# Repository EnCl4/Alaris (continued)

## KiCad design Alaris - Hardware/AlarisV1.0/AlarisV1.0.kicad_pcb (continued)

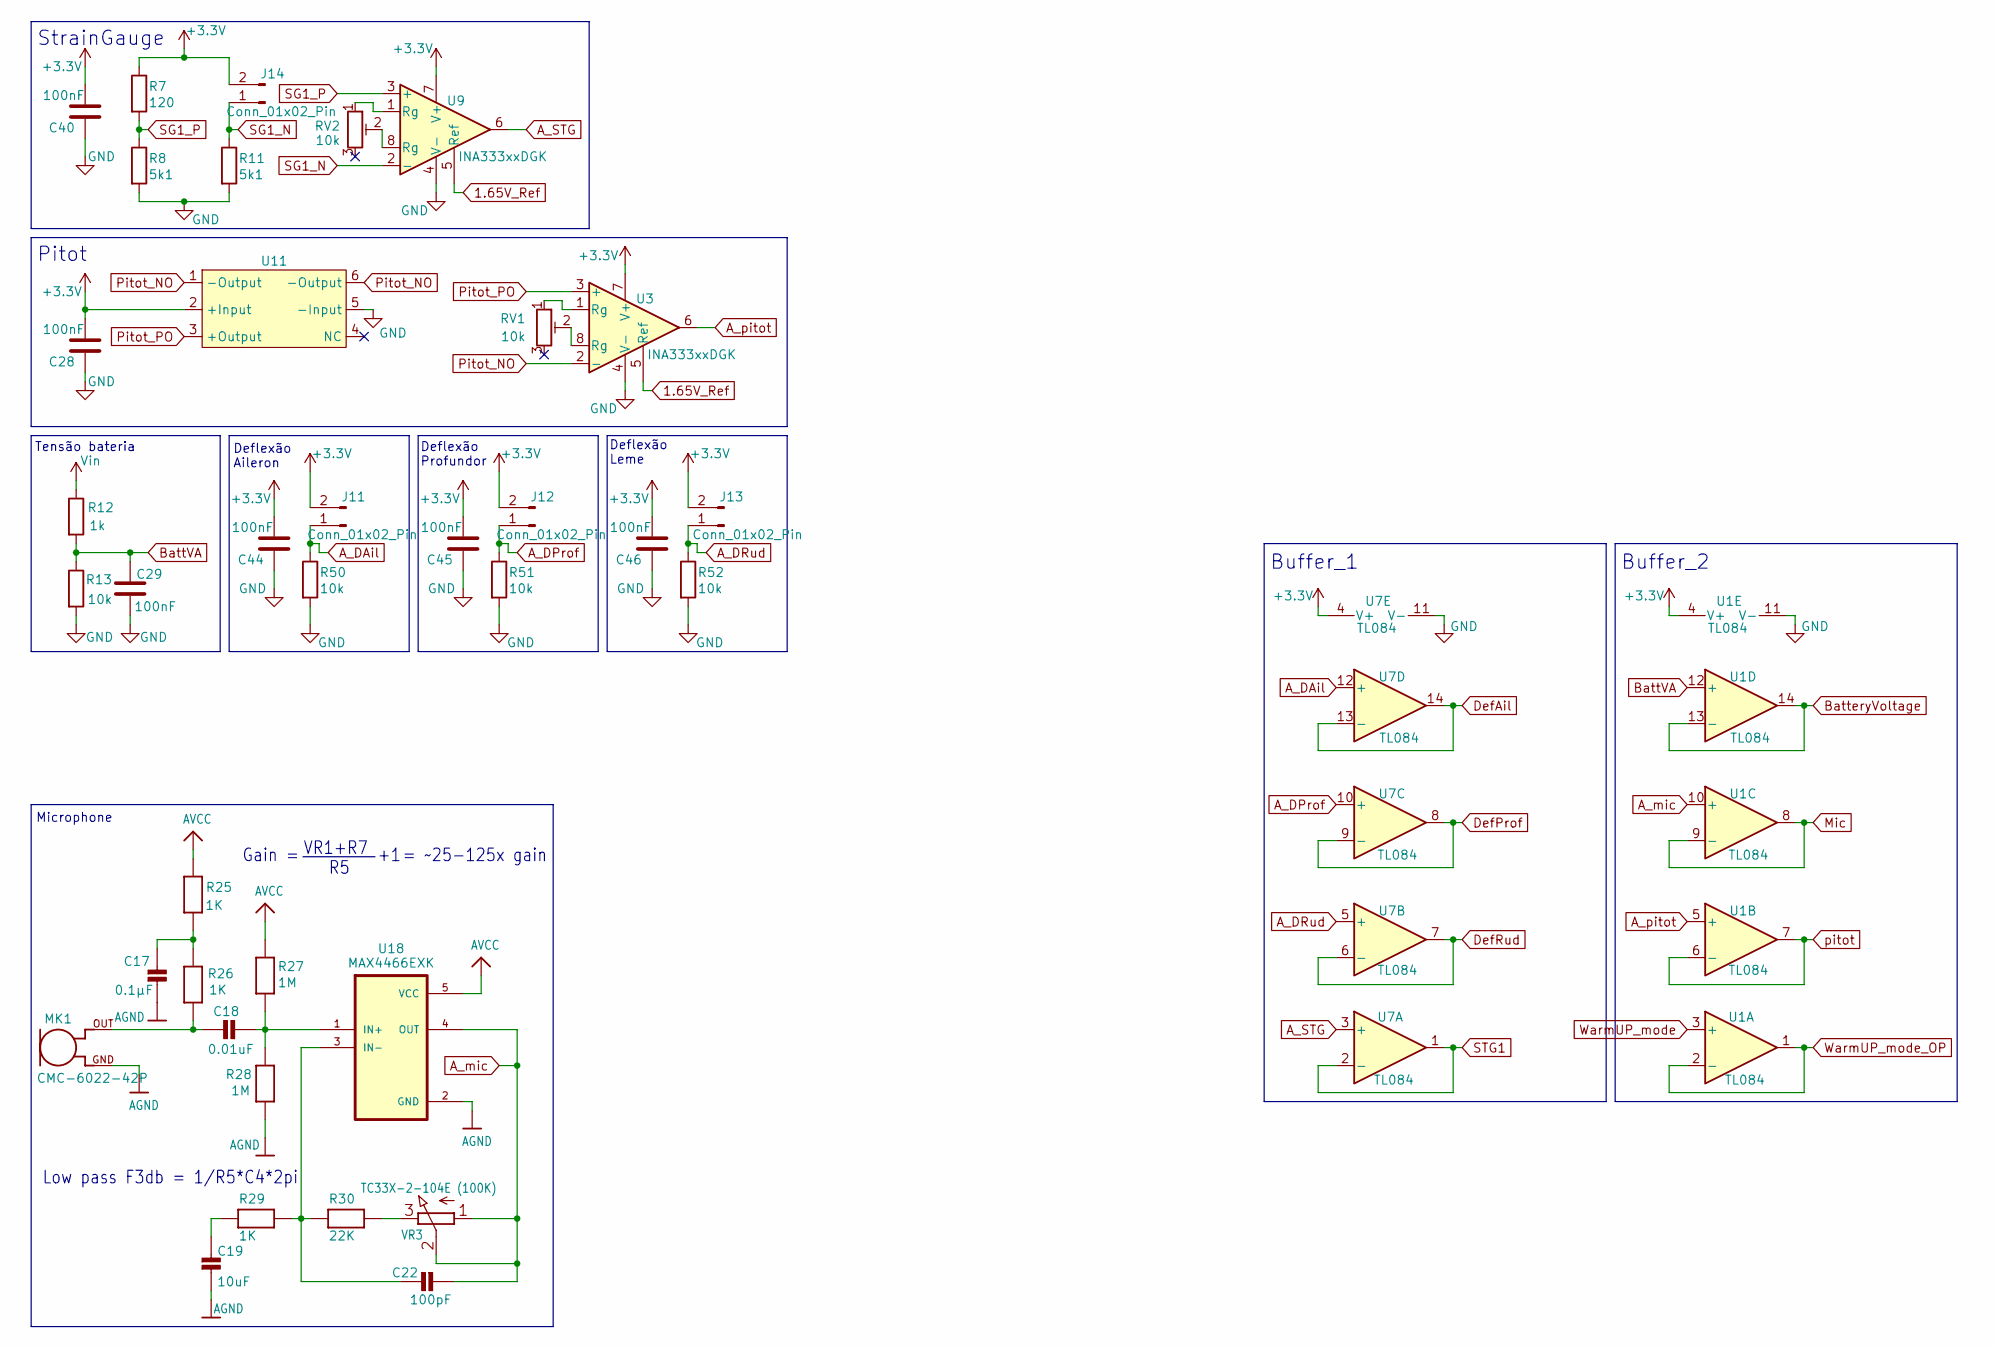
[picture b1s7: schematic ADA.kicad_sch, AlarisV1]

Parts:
C17: 0.1µF; C_0603_1608Metric_Pad1.08x0.95mm_HandSolder
C18: 0.01uF; C_0603_1608Metric_Pad1.08x0.95mm_HandSolder
C19: 10uF; C_0603_1608Metric_Pad1.08x0.95mm_HandSolder
C22: 100pF; C_0603_1608Metric_Pad1.08x0.95mm_HandSolder
C28, C29, C40, C44, C45, C46: 100nF; C_0603_1608Metric_Pad1.08x0.95mm_HandSolder
J11, J12, J13, J14: Conn_01x02_Pin; JST_EH_B2B-EH-A_1x02_P2.50mm_Vertical
MK1: CMC-6022-42P; Mic6022; PARTREV 1
R7: 120; R_0603_1608Metric_Pad0.98x0.95mm_HandSolder
R8, R11: 5k1; R_0603_1608Metric_Pad0.98x0.95mm_HandSolder
R12: 1k; R_0603_1608Metric_Pad0.98x0.95mm_HandSolder
R13, R50, R51, R52: 10k; R_0603_1608Metric_Pad0.98x0.95mm_HandSolder
R25, R26, R29: 1K; R_0603_1608Metric_Pad0.98x0.95mm_HandSolder
R27, R28: 1M; R_0603_1608Metric_Pad0.98x0.95mm_HandSolder
R30: 22K; R_0603_1608Metric_Pad0.98x0.95mm_HandSolder
RV1, RV2: 10k; Potentiometer_Bourns_TC33X_Vertical
U1, U7: TL084; SOIC-14_3.9x8.7mm_P1.27mm
U3, U9: INA333xxDGK; VSSOP-8_3x3mm_P0.65mm
U11: MPS20N0040D
U18: MAX4466EXK; MAX4466
VR3: TC33X-2-104E (100K); Potentiometer_Bourns_TC33X_Vertical

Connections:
1.65V_Ref: U3.5 (Ref), U9.5 (Ref); also elsewhere on the board
+3.3V: C28.2, C40.2, C44.2, C45.2, C46.2, J11.2, J12.2, J13.2, J14.2, R7.1, U1.4 (V+), U3.7 (V+), U7.4 (V+), U9.7 (V+), U11.2 (+Input); also elsewhere on the board
AGND: C17.2, C19.2, MK1.GND, R28.1, U18.2 (GND); also elsewhere on the board
AVCC: R25.2, R27.2, U18.5 (VCC); also elsewhere on the board
A_DAil: J11.1, R50.1, U7.12 (+)
A_DProf: J12.1, R51.1, U7.10 (+)
A_DRud: J13.1, R52.1, U7.5 (+)
A_STG: U7.3 (+), U9.6
A_mic: C22.1, U1.10 (+), U18.4 (OUT), VR3.1 (A), VR3.2 (S)
A_pitot: U1.5 (+), U3.6
BattVA: C29.1, R12.2, R13.1, U1.12 (+)
BatteryVoltage: U1.13 (-), U1.14; also elsewhere on the board
DefAil: U7.13 (-), U7.14; also elsewhere on the board
DefProf: U7.8, U7.9 (-); also elsewhere on the board
DefRud: U7.6 (-), U7.7; also elsewhere on the board
GND: C28.1, C29.2, C40.1, C44.1, C45.1, C46.1, R8.2, R11.2, R13.2, R50.2, R51.2, R52.2, U1.11 (V-), U3.4 (V-), U7.11 (V-), U9.4 (V-), U11.5 (-Input); also elsewhere on the board
Mic: U1.8, U1.9 (-); also elsewhere on the board
unnamed: C17.1, R25.1, R26.2
unnamed: C18.1, MK1.OUT, R26.1
unnamed: C18.2, R27.1, R28.2, U18.1 (IN+)
unnamed: C19.1, R29.1
unnamed: C22.2, R29.2, R30.1, U18.3 (IN-)
unnamed: RV1.1, U3.1 (Rg)
unnamed: RV1.2, U3.8 (Rg)
unnamed: RV2.1, U9.1 (Rg)
unnamed: RV2.2, U9.8 (Rg)
unnamed: R30.2, VR3.3 (E)
Pitot_NO: U3.2 (-), U11.1 (-Output), U11.6 (-Output)
Pitot_PO: U3.3 (+), U11.3 (+Output)
SG1_N: J14.1, R11.1, U9.2 (-)
SG1_P: R7.2, R8.1, U9.3 (+)
STG1: U7.1, U7.2 (-); also elsewhere on the board
Vin: R12.1; also elsewhere on the board
WarmUP_mode: U1.3 (+); also elsewhere on the board
WarmUP_mode_OP: U1.1, U1.2 (-); also elsewhere on the board
pitot: U1.6 (-), U1.7; also elsewhere on the board

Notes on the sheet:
Tensão bateria
StrainGauge
Deflexão Aileron
Microphone
Buffer_1
Deflexão Leme
Gain =
Buffer_2
Low pass F3db = 1/R5*C4*2pi
Deflexão Profundor
VR1+R7
Pitot
= ~25-125x gain

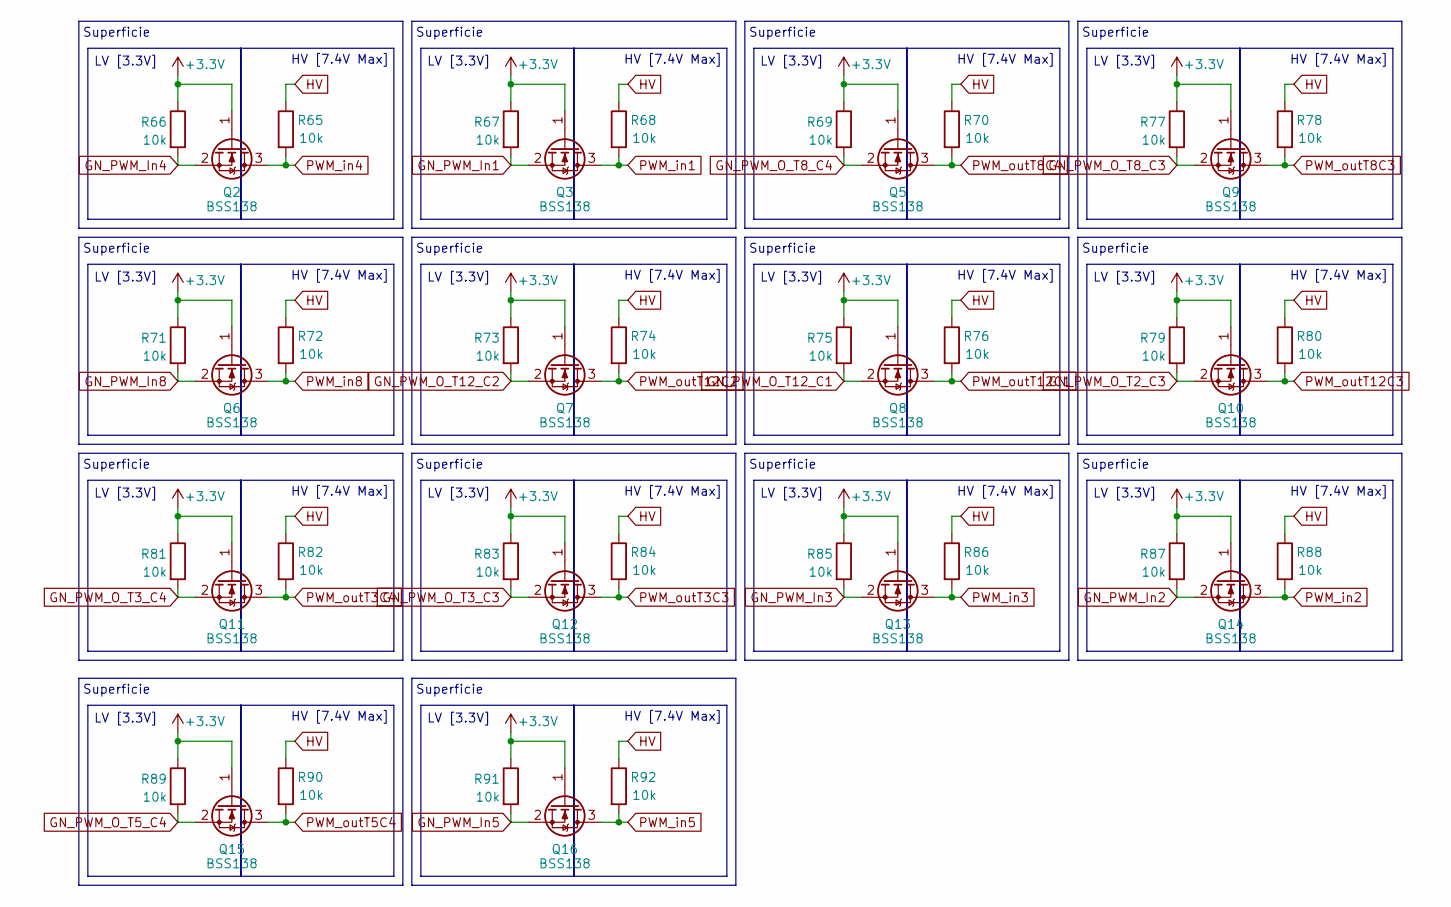
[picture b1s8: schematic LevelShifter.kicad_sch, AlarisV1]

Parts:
Q2, Q3, Q5, Q6, Q7, Q8, Q9, Q10, Q11, Q12, Q13, Q14, Q15, Q16: BSS138; SOT-23
R65, R66, R67, R68, R69, R70, R71, R72, R73, R74, R75, R76, R77, R78, R79, R80, R81, R82, R83, R84, R85, R86, R87, R88, R89, R90, R91, R92: 10k; R_0603_1608Metric_Pad0.98x0.95mm_HandSolder

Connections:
+3.3V: Q2.1 (G), Q3.1 (G), Q5.1 (G), Q6.1 (G), Q7.1 (G), Q8.1 (G), Q9.1 (G), Q10.1 (G), Q11.1 (G), Q12.1 (G), Q13.1 (G), Q14.1 (G), Q15.1 (G), Q16.1 (G), R66.1, R67.1, R69.1, R71.1, R73.1, R75.1, R77.1, R79.1, R81.1, R83.1, R85.1, R87.1, R89.1, R91.1; also elsewhere on the board
GN_PWM_In1: Q3.2 (S), R67.2; also elsewhere on the board
GN_PWM_In2: Q14.2 (S), R87.2; also elsewhere on the board
GN_PWM_In3: Q13.2 (S), R85.2; also elsewhere on the board
GN_PWM_In4: Q2.2 (S), R66.2; also elsewhere on the board
GN_PWM_In5: Q16.2 (S), R91.2; also elsewhere on the board
GN_PWM_In8: Q6.2 (S), R71.2; also elsewhere on the board
GN_PWM_O_T2_C3: Q10.2 (S), R79.2; also elsewhere on the board
GN_PWM_O_T3_C3: Q12.2 (S), R83.2; also elsewhere on the board
GN_PWM_O_T3_C4: Q11.2 (S), R81.2; also elsewhere on the board
GN_PWM_O_T5_C4: Q15.2 (S), R89.2; also elsewhere on the board
GN_PWM_O_T8_C3: Q9.2 (S), R77.2; also elsewhere on the board
GN_PWM_O_T8_C4: Q5.2 (S), R69.2; also elsewhere on the board
GN_PWM_O_T12_C1: Q8.2 (S), R75.2; also elsewhere on the board
GN_PWM_O_T12_C2: Q7.2 (S), R73.2; also elsewhere on the board
HV: R65.1, R68.1, R70.1, R72.1, R74.1, R76.1, R78.1, R80.1, R82.1, R84.1, R86.1, R88.1, R90.1, R92.1; also elsewhere on the board
PWM_in1: Q3.3 (D), R68.2; also elsewhere on the board
PWM_in2: Q14.3 (D), R88.2; also elsewhere on the board
PWM_in3: Q13.3 (D), R86.2; also elsewhere on the board
PWM_in4: Q2.3 (D), R65.2; also elsewhere on the board
PWM_in5: Q16.3 (D), R92.2; also elsewhere on the board
PWM_in8: Q6.3 (D), R72.2; also elsewhere on the board
PWM_outT3C3: Q12.3 (D), R84.2; also elsewhere on the board
PWM_outT3C4: Q11.3 (D), R82.2; also elsewhere on the board
PWM_outT5C4: Q15.3 (D), R90.2; also elsewhere on the board
PWM_outT8C3: Q9.3 (D), R78.2; also elsewhere on the board
PWM_outT8C4: Q5.3 (D), R70.2; also elsewhere on the board
PWM_outT12C1: Q8.3 (D), R76.2; also elsewhere on the board
PWM_outT12C2: Q7.3 (D), R74.2; also elsewhere on the board
PWM_outT12C3: Q10.3 (D), R80.2; also elsewhere on the board

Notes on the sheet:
HV [7.4V Max]
LV [3.3V]
Superficie

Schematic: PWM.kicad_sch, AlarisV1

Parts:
J8, J9, J10, J15, J16, J17, J18, J19, J20, J21, J22, J23, J24, J25: Conn_01x03_Pin; JST_EH_B3B-EH-A_1x03_P2.50mm_Vertical

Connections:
GND: J8.3, J9.3, J10.3, J15.3, J16.3, J17.3, J18.3, J19.3, J20.3, J21.3, J22.3, J23.3, J24.3, J25.3; also elsewhere on the board
HV: J8.2, J9.2, J10.2, J15.2, J16.2, J17.2, J18.2, J19.2, J20.2, J21.2, J22.2, J23.2, J24.2, J25.2; also elsewhere on the board
PWM_in1: J9.1; also elsewhere on the board
PWM_in2: J23.1; also elsewhere on the board
PWM_in3: J22.1; also elsewhere on the board
PWM_in4: J8.1; also elsewhere on the board
PWM_in5: J25.1; also elsewhere on the board
PWM_in8: J15.1; also elsewhere on the board
PWM_outT3C3: J20.1; also elsewhere on the board
PWM_outT3C4: J21.1; also elsewhere on the board
PWM_outT5C4: J24.1; also elsewhere on the board
PWM_outT8C3: J16.1; also elsewhere on the board
PWM_outT8C4: J10.1; also elsewhere on the board
PWM_outT12C1: J18.1; also elsewhere on the board
PWM_outT12C2: J19.1; also elsewhere on the board
PWM_outT12C3: J17.1; also elsewhere on the board

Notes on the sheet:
Signal

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
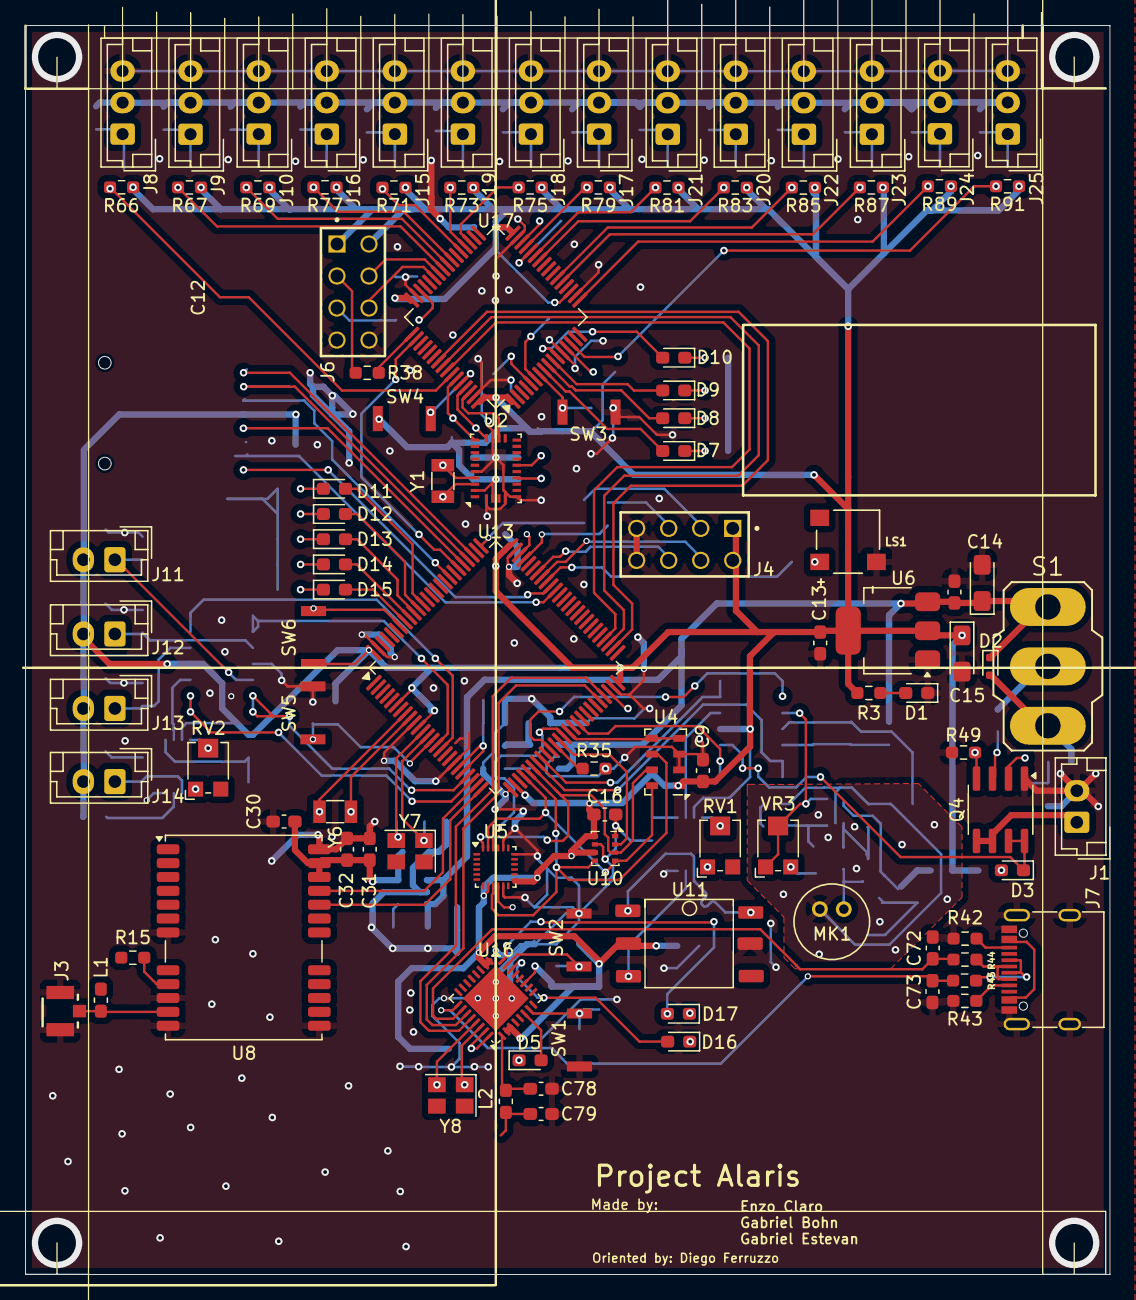
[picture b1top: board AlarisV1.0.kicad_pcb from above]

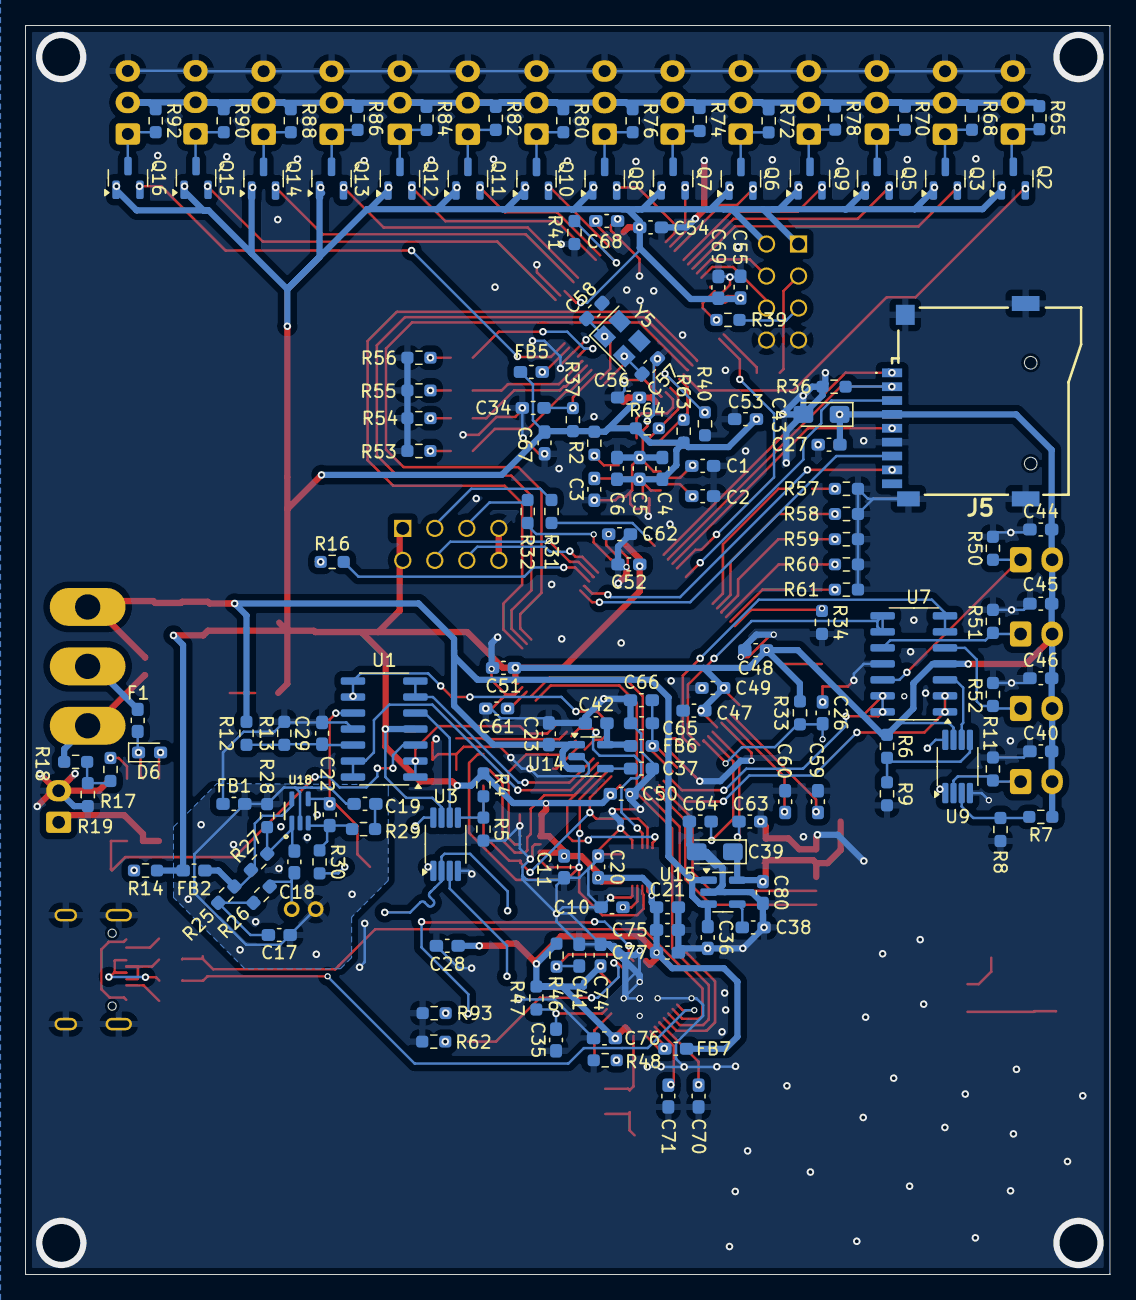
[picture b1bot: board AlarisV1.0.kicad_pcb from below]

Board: 2 copper layers, 86.0 x 99.1 mm, 258 parts (155 on the bottom side), 177 nets.

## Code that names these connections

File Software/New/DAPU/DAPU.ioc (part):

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board=custom
Mcu.Name=STM32H723VGTx
Mcu.Package=LQFP100
Mcu.UserName=STM32H723VGTx
PA0.Mode=IN16-Single-Ended
PA0.Signal=ADC1_INP16
PA1.Mode=IN17-Single-Ended
PA1.Signal=ADC1_INP17
PA10.Mode=Asynchronous
PA10.Signal=USART1_RX
PA13(JTMS/SWDIO).Mode=Serial_Wire
PA13(JTMS/SWDIO).Signal=DEBUG_JTMS-SWDIO
PA14(JTCK/SWCLK).Mode=Serial_Wire
PA14(JTCK/SWCLK).Signal=DEBUG_JTCK-SWCLK
PA2.Mode=Asynchronous
PA2.Signal=USART2_TX
PA3.Signal=GPIO_Analog
PA5.GPIO_Speed=GPIO_SPEED_FREQ_VERY_HIGH
PA5.GPIOParameters=GPIO_Speed
PA5.Mode=Full_Duplex_Master
PA5.Signal=SPI1_SCK
PA6.GPIO_Speed=GPIO_SPEED_FREQ_VERY_HIGH
PA6.GPIOParameters=GPIO_Speed
PA6.Mode=Full_Duplex_Master
PA6.Signal=SPI1_MISO
PA7.GPIO_Speed=GPIO_SPEED_FREQ_VERY_HIGH
PA7.GPIOParameters=GPIO_Speed
PA7.Mode=Full_Duplex_Master
PA7.Signal=SPI1_MOSI
PA8.GPIO_Label=Buzzer
PA8.GPIOParameters=GPIO_Label
PA8.Signal=GPIO_Output
PA9.Mode=Asynchronous
PA9.Signal=USART1_TX
PB0.Signal=GPIO_Analog
PB1.Signal=ADCx_INP5
PB10.Mode=Asynchronous
PB10.Signal=USART3_TX
PB11.Mode=Asynchronous
PB11.Signal=USART3_RX
PB13.GPIO_Speed=GPIO_SPEED_FREQ_VERY_HIGH
PB13.GPIOParameters=GPIO_Speed
PB13.Mode=Full_Duplex_Master
PB13.Signal=SPI2_SCK
PB14.GPIO_Speed=GPIO_SPEED_FREQ_VERY_HIGH
PB14.GPIOParameters=GPIO_Speed
PB14.Mode=Full_Duplex_Master
PB14.Signal=SPI2_MISO
PB15.GPIO_Speed=GPIO_SPEED_FREQ_VERY_HIGH
PB15.GPIOParameters=GPIO_Speed
PB15.Mode=Full_Duplex_Master
PB15.Signal=SPI2_MOSI
PB3(JTDO/TRACESWO).GPIO_Label=LED_RUN
PB3(JTDO/TRACESWO).GPIOParameters=GPIO_Label
PB3(JTDO/TRACESWO).Signal=GPIO_Output
PB4(NJTRST).GPIO_Label=LED_SENSORS
PB4(NJTRST).GPIOParameters=GPIO_Label
PB4(NJTRST).Signal=GPIO_Output
PB5.GPIO_Label=LED_SD
PB5.GPIOParameters=GPIO_Label
PB5.Signal=GPIO_Output
PB6.GPIO_Label=LED_GNCU
PB6.GPIOParameters=GPIO_Label
PB6.Signal=GPIO_Output
PB7.GPIO_Label=LED_CGU
PB7.GPIOParameters=GPIO_Label
PB7.Signal=GPIO_Output
PB8.Mode=I2C
PB8.Signal=I2C1_SCL
PB9.Mode=I2C
PB9.Signal=I2C1_SDA
PC0.Signal=ADCx_INP10
PC1.Signal=ADCx_INP11
PC10.Mode=SD_4_bits_Wide_bus
PC10.Signal=SDMMC1_D2
PC11.Mode=SD_4_bits_Wide_bus
PC11.Signal=SDMMC1_D3
PC12.Mode=SD_4_bits_Wide_bus
PC12.Signal=SDMMC1_CK
PC14-OSC32_IN.Mode=LSE-External-Oscillator
PC14-OSC32_IN.Signal=RCC_OSC32_IN
PC15-OSC32_OUT.Mode=LSE-External-Oscillator
PC15-OSC32_OUT.Signal=RCC_OSC32_OUT
PC4.Signal=ADCx_INP4
PC5.Signal=ADCx_INP8
PC8.Mode=SD_4_bits_Wide_bus
PC8.Signal=SDMMC1_D0
PC9.Mode=SD_4_bits_Wide_bus
PC9.Signal=SDMMC1_D1
PD0.GPIO_Speed=GPIO_SPEED_FREQ_VERY_HIGH
PD0.GPIOParameters=GPIO_Speed,PinState
PD0.PinState=GPIO_PIN_SET
PD0.Signal=GPIO_Output
PD2.Mode=SD_4_bits_Wide_bus
PD2.Signal=SDMMC1_CMD
PD6.Mode=Asynchronous
PD6.Signal=USART2_RX
PE10.GPIO_Label=L_workingStatus
PE10.GPIOParameters=GPIO_Label
PE10.Signal=GPIO_Output
PE11.Signal=GPIO_Input
PE12.Mode=Simplex_Bidirectional_Master
PE12.Signal=SPI4_SCK
PE14.Mode=Simplex_Bidirectional_Master
PE14.Signal=SPI4_MOSI
PE2.Signal=GPIO_Output
PE3.GPIO_Label=LED_BOARD
PE3.GPIOParameters=GPIO_Label
PE3.Signal=GPIO_Output
PE4.Signal=GPIO_Output
PE7.GPIO_Label=BMP280_CS
PE7.GPIO_Speed=GPIO_SPEED_FREQ_VERY_HIGH
PE7.GPIOParameters=GPIO_Speed,PinState,GPIO_Label
PE7.PinState=GPIO_PIN_SET
PE7.Signal=GPIO_Output
PE8.GPIO_Label=ICM20948_CS
PE8.GPIO_Speed=GPIO_SPEED_FREQ_VERY_HIGH
PE8.GPIOParameters=GPIO_Speed,PinState,GPIO_Label
PE8.PinState=GPIO_PIN_SET
PE8.Signal=GPIO_Output
PE9.GPIO_Label=MS5611_CS
PE9.GPIO_Speed=GPIO_SPEED_FREQ_VERY_HIGH
PE9.GPIOParameters=GPIO_Speed,PinState,GPIO_Label
PE9.PinState=GPIO_PIN_SET
PE9.Signal=GPIO_Output
PH0-OSC_IN.Mode=HSE-External-Oscillator
PH0-OSC_IN.Signal=RCC_OSC_IN
PH1-OSC_OUT.Mode=HSE-External-Oscillator
PH1-OSC_OUT.Signal=RCC_OSC_OUT
RCC.HSE_VALUE=25000000
RCC.SYSCLKFreq_VALUE=200000000
RCC.SYSCLKSource=RCC_SYSCLKSOURCE_PLLCLK

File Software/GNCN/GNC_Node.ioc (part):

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Mcu.Name=STM32F446R(C-E)Tx
Mcu.Package=LQFP64
Mcu.UserName=STM32F446RETx
PA0-WKUP.Signal=S_TIM5_CH1
PA1.Signal=S_TIM5_CH2
PA10.Mode=Asynchronous
PA10.Signal=USART1_RX
PA11.Signal=S_TIM1_CH4
PA13.Mode=Serial_Wire
PA13.Signal=SYS_JTMS-SWDIO
PA14.Mode=Serial_Wire
PA14.Signal=SYS_JTCK-SWCLK
PA15.Mode=NSS_Signal_Hard_Input
PA15.Signal=SPI1_NSS
PA2.Signal=S_TIM5_CH3
PA3.Signal=S_TIM5_CH4
PA5.Signal=S_TIM2_CH1_ETR
PA6.Signal=S_TIM3_CH1
PA7.Signal=S_TIM3_CH2
PA8.Signal=S_TIM1_CH1
PA9.Mode=Asynchronous
PA9.Signal=USART1_TX
PB0.Signal=S_TIM3_CH3
PB1.Signal=S_TIM3_CH4
PB10.Signal=S_TIM2_CH3
PB14.Signal=S_TIM12_CH1
PB15.Signal=S_TIM12_CH2
PB2.Signal=S_TIM2_CH4
PB3.Mode=Full_Duplex_Slave
PB3.Signal=SPI1_SCK
PB4.Mode=Full_Duplex_Slave
PB4.Signal=SPI1_MISO
PB5.Mode=Full_Duplex_Slave
PB5.Signal=SPI1_MOSI
PB6.Signal=S_TIM4_CH1
PB7.Mode=I2C
PB7.Signal=I2C1_SDA
PB8.Mode=I2C
PB8.Signal=I2C1_SCL
PB9.Signal=S_TIM2_CH2
PC14-OSC32_IN.Mode=LSE-External-Oscillator
PC14-OSC32_IN.Signal=RCC_OSC32_IN
PC15-OSC32_OUT.Mode=LSE-External-Oscillator
PC15-OSC32_OUT.Signal=RCC_OSC32_OUT
PC6.Signal=S_TIM8_CH1
PC8.Signal=S_TIM8_CH3
PC9.Signal=S_TIM8_CH4
PH0-OSC_IN.Mode=HSE-External-Oscillator
PH0-OSC_IN.Signal=RCC_OSC_IN
PH1-OSC_OUT.Mode=HSE-External-Oscillator
PH1-OSC_OUT.Signal=RCC_OSC_OUT
RCC.SYSCLKFreq_VALUE=180000000
RCC.SYSCLKSource=RCC_SYSCLKSOURCE_PLLCLK
board=custom

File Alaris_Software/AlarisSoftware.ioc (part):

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Mcu.Name=STM32F401R(B-C)Tx
Mcu.Package=LQFP64
Mcu.UserName=STM32F401RCTx
PA0-WKUP.Signal=ADCx_IN0
PA1.Signal=ADCx_IN1
PA10.Mode=Asynchronous
PA10.Signal=USART1_RX
PA13.Mode=Serial_Wire
PA13.Signal=SYS_JTMS-SWDIO
PA14.Mode=Serial_Wire
PA14.Signal=SYS_JTCK-SWCLK
PA2.Mode=Asynchronous
PA2.Signal=USART2_TX
PA3.Mode=Asynchronous
PA3.Signal=USART2_RX
PA4.Signal=ADCx_IN4
PA5.Mode=Full_Duplex_Master
PA5.Signal=SPI1_SCK
PA6.Mode=Full_Duplex_Master
PA6.Signal=SPI1_MISO
PA7.Mode=Full_Duplex_Master
PA7.Signal=SPI1_MOSI
PA8.Mode=I2C
PA8.Signal=I2C3_SCL
PA9.Mode=Asynchronous
PA9.Signal=USART1_TX
PB0.Signal=ADCx_IN8
PB1.Signal=ADCx_IN9
PB10.Mode=Full_Duplex_Master
PB10.Signal=SPI2_SCK
PB14.Mode=Full_Duplex_Master
PB14.Signal=SPI2_MISO
PB15.Mode=Full_Duplex_Master
PB15.Signal=SPI2_MOSI
PB3.GPIOParameters=GPIO_Speed,PinState,GPIO_Label
PB3.GPIO_Label=BMP280_CS
PB3.GPIO_Speed=GPIO_SPEED_FREQ_VERY_HIGH
PB3.PinState=GPIO_PIN_SET
PB3.Signal=GPIO_Output
PB4.GPIOParameters=GPIO_Speed,PinState,GPIO_Label
PB4.GPIO_Label=CS
PB4.GPIO_Speed=GPIO_SPEED_FREQ_VERY_HIGH
PB4.PinState=GPIO_PIN_SET
PB4.Signal=GPIO_Output
PB5.GPIOParameters=GPIO_Speed,PinState,GPIO_Label
PB5.GPIO_Label=ICM20948_CS
PB5.GPIO_Speed=GPIO_SPEED_FREQ_VERY_HIGH
PB5.PinState=GPIO_PIN_SET
PB5.Signal=GPIO_Output
PB9.Signal=GPIO_Output
PC0.Signal=ADCx_IN10
PC1.Signal=ADCx_IN11
PC2.Signal=ADCx_IN12
PC3.Signal=ADCx_IN13
PC4.Signal=ADCx_IN14
PC5.Signal=ADCx_IN15
PC9.Mode=I2C
PC9.Signal=I2C3_SDA
PH0\ -\ OSC_IN.Mode=HSE-External-Oscillator
PH0\ -\ OSC_IN.Signal=RCC_OSC_IN
PH1\ -\ OSC_OUT.Mode=HSE-External-Oscillator
PH1\ -\ OSC_OUT.Signal=RCC_OSC_OUT
RCC.HSE_VALUE=25000000
RCC.SYSCLKFreq_VALUE=84000000
RCC.SYSCLKSource=RCC_SYSCLKSOURCE_PLLCLK
board=custom

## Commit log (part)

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2026-02-18 Integração dos sensores
2026-03-01 Desenvolvimento do Hardware
    Desenvolvido os modulos de DAPN, GNCN, LDIN
    Ainda é necessario implementação de alguns sensores, e melhor o modulo de gerenciamento de energia da placa
2026-03-02 Hardware and Software
    Hardware: adição da proteção contra polaridade reversa
    Software: Adição dos arquivos iniciais de projeto do LDIN
2026-04-19 Desenvolvimento da PCB
2026-05-10 Mudanças GNCN
    Adição do acelerômetro de backup
    Mudanças no PWM read
    Adição da comunicação entre núcleos utilizando SPI
2026-05-21 Mudanças preparatorias para PID
    Finalização da adição da emissão dos sinais PWM para controle dos servos
    Criação de uma estrurura base/função do PID. Necessario revisar e verificar variavel de tempo a partir do clock do sistema, e definir prioridade da função
2026-05-25 Malha de controle de phi
    Adição das tasks e funções de controle basica para o phi
